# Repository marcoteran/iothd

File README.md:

---
<div align="center">

# Diseño de dispositivos para el Internet de las Cosas - 2023-II

</div>

---
## Descripción del curso

El curso **Diseño de dispositivos para el Internet de las Cosas**  es una introducción al diseño y análisis de dispositivos para el Internet de las Cosas.
* Se estudiarán los principios de diseño de productos electrónicos enfocados al Internet de las Cosas en cada una de las etapas asociadas:
	- Desde la idea y concepción hasta el desarrollo del producto

#### Información de contacto:
* **Profesor:** [Marco Teran](https://marcoteran.github.io/)
* **Telegram group:** [https://t.me/+rxKaBlR8DTw5YmRh](https://t.me/+rxKaBlR8DTw5YmRh)
---

## Contenido
0. **Presentación del curso *Diseño de dispositivos para el Internet de las Cosas***
	* Descargar presentación [[PDF]](https://github.com/marcoteran/iothd/raw/master/lectures/00_iothd_syllabus.pdf)
1. **Internet de las Cosas y aplicaciones**
	* Descargar presentación [[PDF]](https://github.com/marcoteran/iothd/raw/master/lectures/01_iothd_iotapplications.pdf)
2. **Proceso de diseño en ingeniería**
	* Descargar presentación [[PDF]](https://github.com/marcoteran/iothd/raw/master/lectures/02_iothd_designprocess.pdf)
3. **Metodología SCRUM**
	* Descargar presentación [[PDF]](https://github.com/marcoteran/iothd/raw/master/lectures/03_iothd_scrum.pdf)
	* *Notas: Metodología SCRUM* [[PDF]](https://github.com/marcoteran/iothd/raw/master/resources/literature/iothd_scrum.pdf)
4. **Curso de GIT y control de versiones**
	* Descargar presentación [PDF](https://github.com/marcoteran/iothd/raw/master/lectures/04_iothd_git.pdf)
		- **Manual GIT y control de versiones** [Descargar](https://github.com/marcoteran/iothd/raw/master/resources/cheatsheets/iothd_gitbook_v0.pdf)
		- **GIT cheat sheets:** 
			[GitHub](https://github.com/marcoteran/iothd/raw/master/resources/cheatsheets/github_gitcheatsheet.pdf)
			[Datacamp](https://github.com/marcoteran/iothd/raw/master/resources/cheatsheets/datacamp_gitcheatsheet.pdf)
			[Gitlab](https://github.com/marcoteran/iothd/raw/master/resources/cheatsheets/gitlab_gitcheatsheet.pdf)
			[Atlassian](https://github.com/marcoteran/iothd/raw/master/resources/cheatsheets/atlassian_gitcheatsheet.pdf)
		- **Vídeo:** Introduction to Git Recap | Learn with Dr G. [[YT]](https://www.youtube.com/watch?v=9uGS1ak_FGg&ab_channel=MicrosoftDeveloper)
		- Quick reference guides: GitHub Cheat Sheet [[Visual Git Cheat Sheet]](https://ndpsoftware.com/git-cheatsheet.html#loc=index;)
		- **Curso:** Introducción al control de versiones con Git [[LINK]](https://learn.microsoft.com/es-es/training/paths/intro-to-vc-git/)
5. **Fundamentos de diseño de circuitos impresos**
	* Descargar presentación [PDF](https://github.com/marcoteran/iothd/raw/master/lectures/05_iothd_pcbdesign.pdf)

---
## Bibliografía
1. Bahga, A., & Madisetti, V. (2017). Internet of Things: A Hands-On Approach. VPT.

---

<div align="center">

Hecho con ❤️ por [Marco Teran](https://github.com/marcoteran)

</div>

---

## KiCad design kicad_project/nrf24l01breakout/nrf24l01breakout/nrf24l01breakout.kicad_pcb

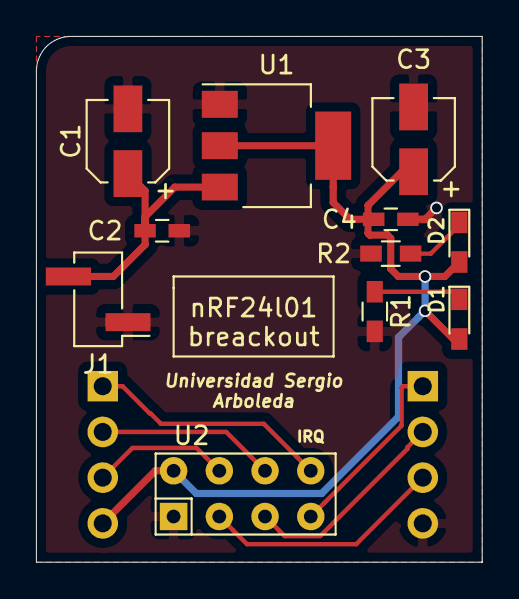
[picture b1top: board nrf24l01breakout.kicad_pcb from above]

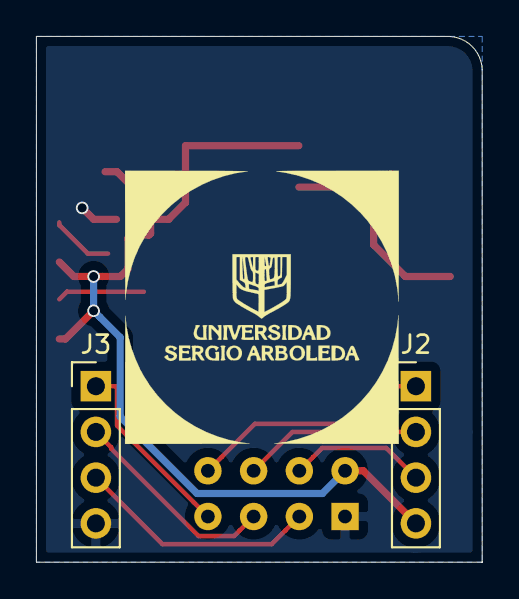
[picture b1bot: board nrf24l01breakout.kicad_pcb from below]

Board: 2 copper layers, 24.8 x 29.2 mm, 13 parts (2 on the bottom side), 11 nets.

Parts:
C1, C3: 10u; CP_Elec_4x5.7
C2, C4: 104; C_0603_HandSoldering
D1, D2: LED; LED_0603_HandSoldering
J1: Conn_01x02; Pin_Header_Straight_1x02_Pitch2.54mm_SMD_Pin1Left
J2, J3: Conn_01x04_Male; Pin_Header_Straight_1x04_Pitch2.54mm
R1, R2: 1k; R_0603_HandSoldering
U1: LM1117-3.3; SOT-223-3_TabPin2
U2: nRF24L01_breakout; nrf24l01_breackout

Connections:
3.3V: C3.1, C4.1, D1.2, D2.2, J2.4, U1.2, U2.2
/CE: J3.3, U2.3
/IRQ: J2.1, U2.8
/MISO: J3.1, U2.7
/MOSI: J2.2, U2.6
/SCK: J3.2, U2.5
/~CSN: J2.3, U2.4
GND: C1.2, C2.2, C3.2, C4.2, J1.1, J3.4, R1.2, R2.2, U1.1, U2.1
unnamed: D1.1, R1.1
unnamed: D2.1, R2.1
VCC: C1.1, C2.1, J1.2, U1.3

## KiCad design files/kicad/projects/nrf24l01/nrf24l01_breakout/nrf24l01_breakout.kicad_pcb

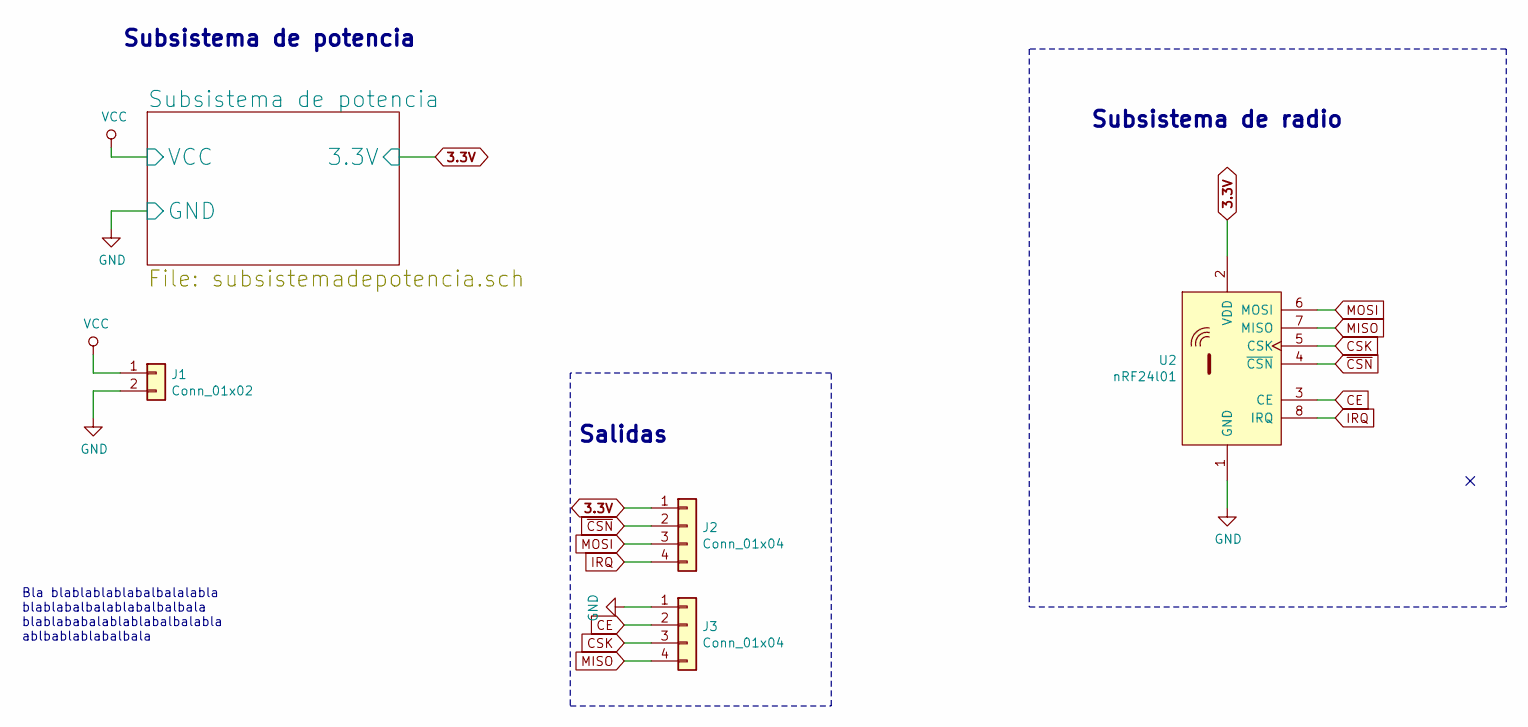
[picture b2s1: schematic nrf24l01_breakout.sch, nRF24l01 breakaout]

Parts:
J1: Conn_01x02; Pin_Header_Straight_1x02_Pitch2.54mm
J2, J3: Conn_01x04; Pin_Header_Straight_1x04_Pitch2.54mm
U2: nRF24l01; nrf24l01

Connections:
3.3V: J2.1, U2.2 (VDD); also elsewhere on the board
CE: J3.2, U2.3 (CE)
CSK: J3.3, U2.5 (CSK)
GND: J1.2, J3.1, U2.1 (GND); also elsewhere on the board
IRQ: J2.4, U2.8 (IRQ)
MISO: J3.4, U2.7 (MISO)
MOSI: J2.3, U2.6 (MOSI)
VCC: J1.1; also elsewhere on the board
~CSN: J2.2, U2.4 (~CSN)

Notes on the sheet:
Subsistema de potencia
Salidas
Subsistema de radio
Bla blablablablabalbalalabla blablabalbalablabalbalbala blablababalablablabalbalabla ablbablablabalbala

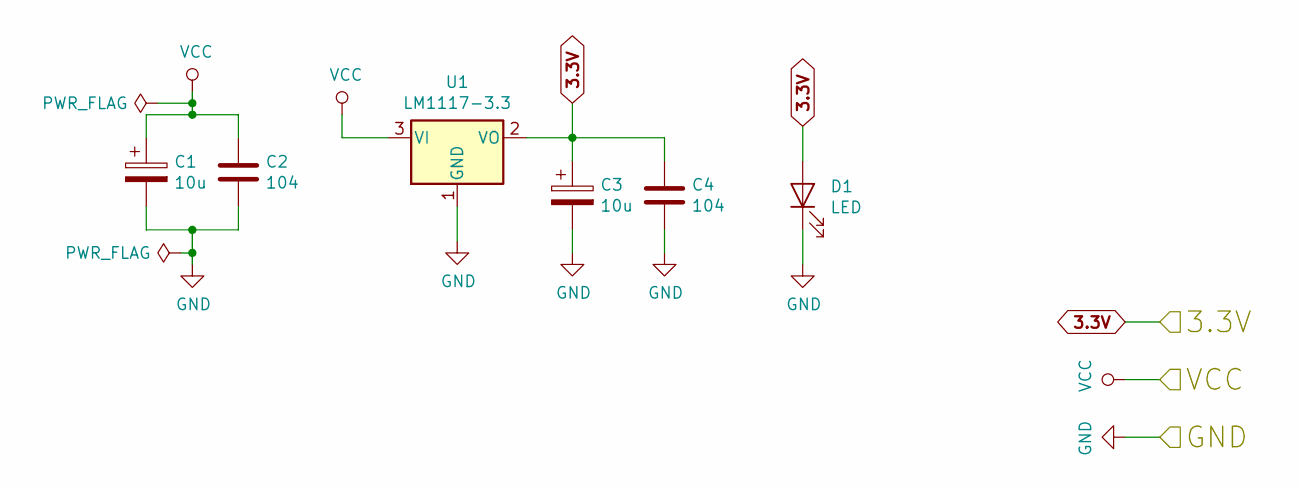
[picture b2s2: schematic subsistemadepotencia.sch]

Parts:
C1, C3: 10u; CP_Elec_6.3x5.7
C2, C4: 104; C_0603_HandSoldering
D1: LED; LED_0603_HandSoldering
U1: LM1117-3.3; SOT-223-3_TabPin2

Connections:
3.3V: C3.1, C4.1, D1.2 (A), U1.2 (VO); also elsewhere on the board
GND: C1.2, C2.2, C3.2, C4.2, D1.1 (K), U1.1 (GND); also elsewhere on the board
VCC: C1.1, C2.1, U1.3 (VI); also elsewhere on the board

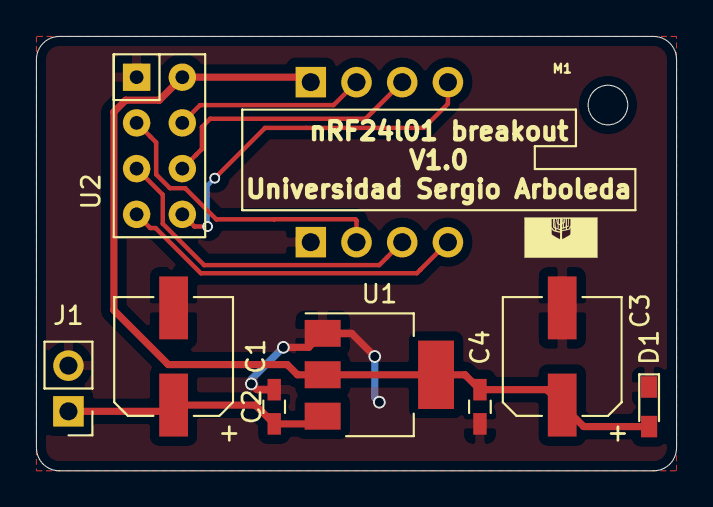
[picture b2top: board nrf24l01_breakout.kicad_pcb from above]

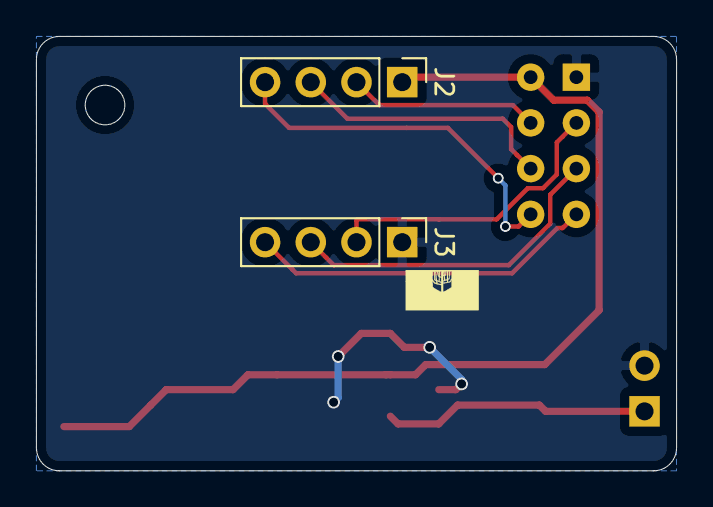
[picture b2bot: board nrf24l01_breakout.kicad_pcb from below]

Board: 2 copper layers, 35.6 x 24.1 mm, 11 parts (2 on the bottom side), 9 nets.

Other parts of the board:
M1: MountingHole_2.2mm_M2

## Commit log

2023-01-23 upd all the info
2023-01-23 fixed banner
2023-01-23 added new iot and apps
2023-01-24 corrected slides
2023-01-30 added slide edp
2023-02-06 added EDS
2023-02-13 added pry packages
2023-02-20 added scrum met
2023-02-28 added github info
2023-02-28 added github info 2
2023-03-06 upd git slides
2023-03-07 updated rdm
2023-03-07 updated pos
2023-03-07 updated pos 2
2023-03-14 upd gitbook
2023-04-10 added pcb design
2023-04-17 added kicad files
2023-05-05 upd rdm
2023-07-23 started to work 2023II
2023-07-24 upd info
2023-07-24 added syllabus
2023-07-26 added slide iot apps
2023-07-31 added edp slide
2023-08-14 added scrum
2023-08-30 added git material
2023-09-11 added pcb desing
